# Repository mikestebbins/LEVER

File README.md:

Mike's notes (2016-01-04)
1. schematic and silk screen say 2.2 uF capacitor for C1, but link to part in BOM is for a 2200 pF, or 0.0022 uF
2. 220k resistor spec'd in BOM is WAY too small for pad on board, had to use jumper wire that looks about 50% successful.
3. Arduino code is all for encoder (except for board testing code), but Eagle Board/Schematic files don't seem to have all the necessary hook-ups for encoder to Teensy.
4. May have screwed up and forgot to cut Teensy's trace for battery operation before soldering to board.

# LEVER
####Experiments in electrovibration interaction strategies, inspired by Disney Research papers "Tesla Touch" and "Revel"

Here are the papers I am trying to implement here:
http://www.ivanpoupyrev.com/e-library/2010/teslatouchUIST2010.pdf

http://www.disneyresearch.com/wp-content/uploads/REVEL.pdf

###Summary
Basically, the papers describe a way to augment surfaces with _dynamically changeable tactile properties_ - a surface can change from sticky to slippery basically at will.

###Status
This work is incomplete and ongoing - for one thing, while the circuit decribed here works, I have yet to implement current-sensing feedback as described in the papers. I'm eager to accomplish this because it allows normalization of sensation across people, skin moistures, and time.

###Why I am interested
I'm interested in experimenting with this technology as applied to various notification strategies, particularly on mobile and wearable devices.
I would like to develop interactions in which a person queries a "stack" of stuff waiting for them, rather than being interrupted by a push notification.
The appeal of this technology in this application is that it's totally silent and able to be done without interrupting the person's conversation by stealing focus.
If this technology is implemented on the back of a mobile device, for example, simply rubbing a finger along the back of the phone is all that is needed to see the magnitude of my "stack."
Of course, "stack" can be many things: number of unread emails, number of to-do items, number of places of interest very near me, and so on.

###This repository
The purpose of this repo is to make my work shareable - I had a fair amount of trouble trying to go from the research paper to a safe, working circuit, and I'm hoping to save others some work.

The circuitboard isn't what I would put onto a phone - it is instead a platform for trying out different waveforms, intensities, and so on.

The intent is that you will use the board to figure out the correct implementation details and then generate your own board with a more appropriate layout.

###Requirements
You should follow the BOM pretty precisely unless you know what you are doing. The circuit is designed to work with a 9v battery and I will be trying to allow smaller/more power supplies to work with it. The microcontroller is a Teensy 3.1

###Thanks
I'm so grateful to Disney Research, Ivan Poupyrev, Olivier Bau, and others who worked on the papers for making their work available - I never would have known aobut this cool phoneomenon without their shared work! Thanks as well to nytlabs for supporting my explorations and letting me share in kind.

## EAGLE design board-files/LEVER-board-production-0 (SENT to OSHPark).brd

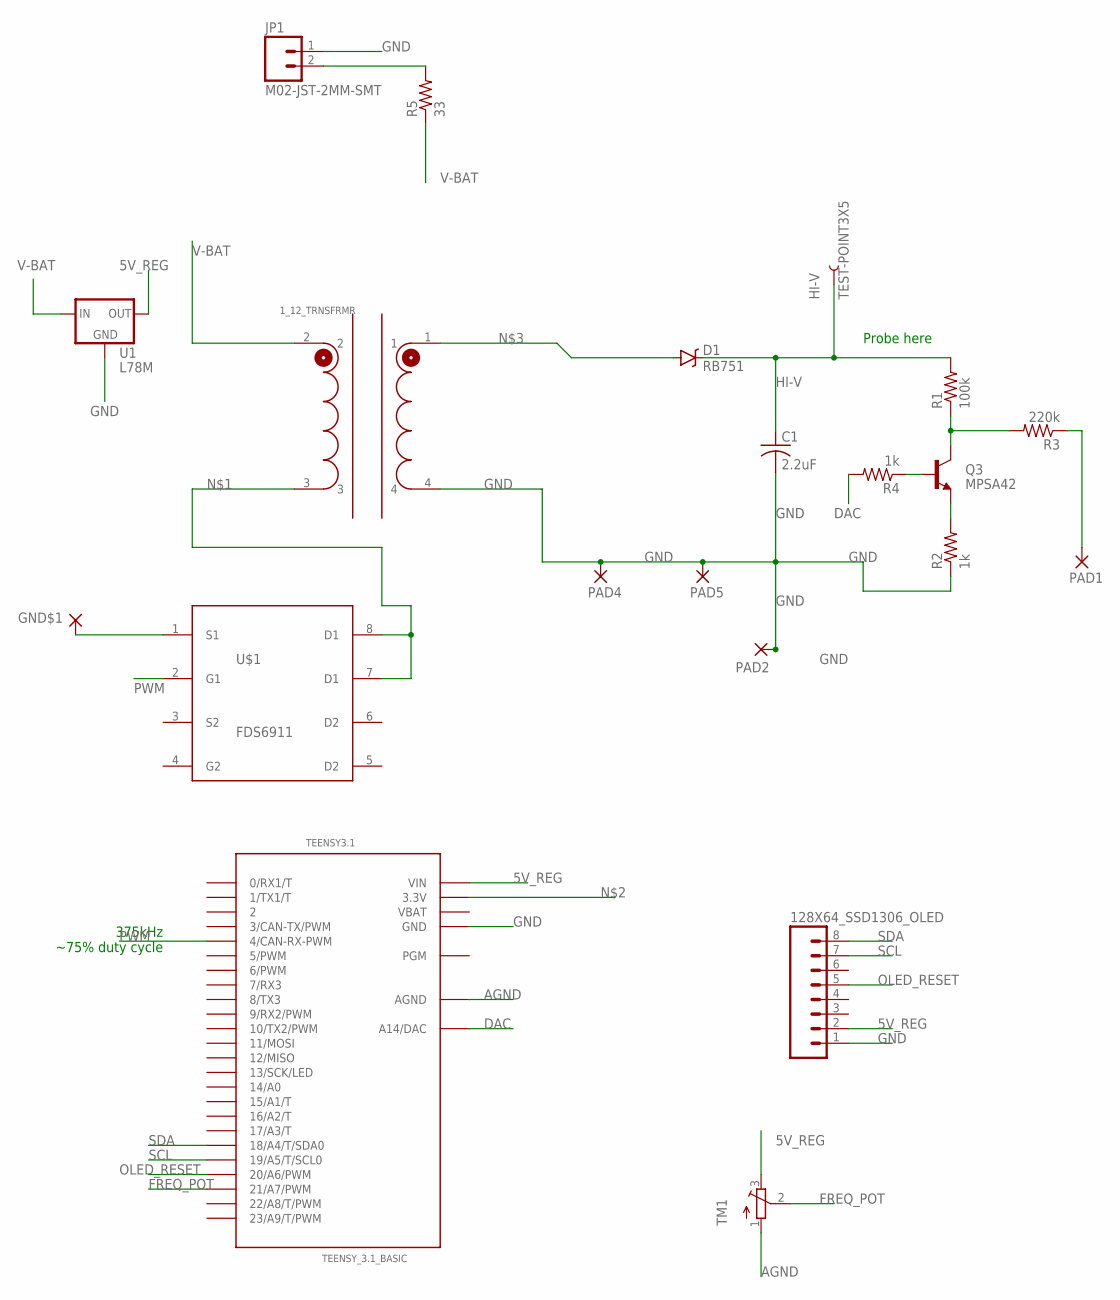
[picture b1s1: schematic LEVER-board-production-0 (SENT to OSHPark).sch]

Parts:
1_12_TRNSFRMR: PA0367
128X64_SSD1306_OLED: M08LOCK; 1X08_LOCK
C1: 2.2uF; C1812
D1: RB751; TO263
GND$1: WIREPADSMD5-2,5; 5-2,5
HI-V: TEST-POINT3X5; PAD.03X.05
JP1: M02-JST-2MM-SMT; JST-2-SMD
PAD1, PAD2, PAD4, PAD5: WIREPADSMD5-2,5; 5-2,5
Q3: MPSA42; TO-92
R1: 100k; R2010
R2, R4: 1k; 1206
R3: 220k; R2010
R5: 33; 1206
TEENSY3.1: TEENSY_3.1_BASIC
TM1: TRIMPOT3386; TRIM-3386
U1: L78M; DPAK
U$1: FDS6911; SO8

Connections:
5V_REG: 128X64_SSD1306_OLED.2, TEENSY3.1.VIN, TM1.3 (E), U1.3 (OUT)
AGND: TEENSY3.1.AGND, TM1.1 (A)
DAC: R4.2, TEENSY3.1.A14 (A14/DAC)
FREQ_POT: TEENSY3.1.21/A7 (21/A7/PWM), TM1.2 (S)
GND: 1_12_TRNSFRMR.4, 128X64_SSD1306_OLED.1, C1.2, GND$1.1, JP1.1 (2), PAD2.1, PAD4.1, PAD5.1, R2.1, TEENSY3.1.GND, TEENSY3.1.GND1 (GND), U1.4 (GND), U$1.1 (S1)
HI-V: C1.1, D1.1 (C), HI-V.P$1, R1.2
unnamed: 1_12_TRNSFRMR.3, U$1.7 (D1), U$1.8 (D1)
unnamed: TEENSY3.1.3.3V, TEENSY3.1.3.3V1 (3.3V)
unnamed: 1_12_TRNSFRMR.1, D1.2 (A)
unnamed: JP1.2 (1), R5.2
unnamed: Q3.1 (C), R1.1, R3.2
unnamed: Q3.3 (E), R2.2
unnamed: Q3.2 (B), R4.1
OLED_RESET: 128X64_SSD1306_OLED.5, TEENSY3.1.20/A6 (20/A6/PWM)
PAD: PAD1.1, R3.1
PWM: TEENSY3.1.4 (4/CAN-RX-PWM), U$1.2 (G1)
SCL: 128X64_SSD1306_OLED.7, TEENSY3.1.19/A5 (19/A5/T/SCL0)
SDA: 128X64_SSD1306_OLED.8, TEENSY3.1.18/A4 (18/A4/T/SDA0)
V-BAT: 1_12_TRNSFRMR.2, R5.1, U1.1 (IN)
VBAT: TEENSY3.1.VBAT

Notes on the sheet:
Probe here
375kHz ~75% duty cycle

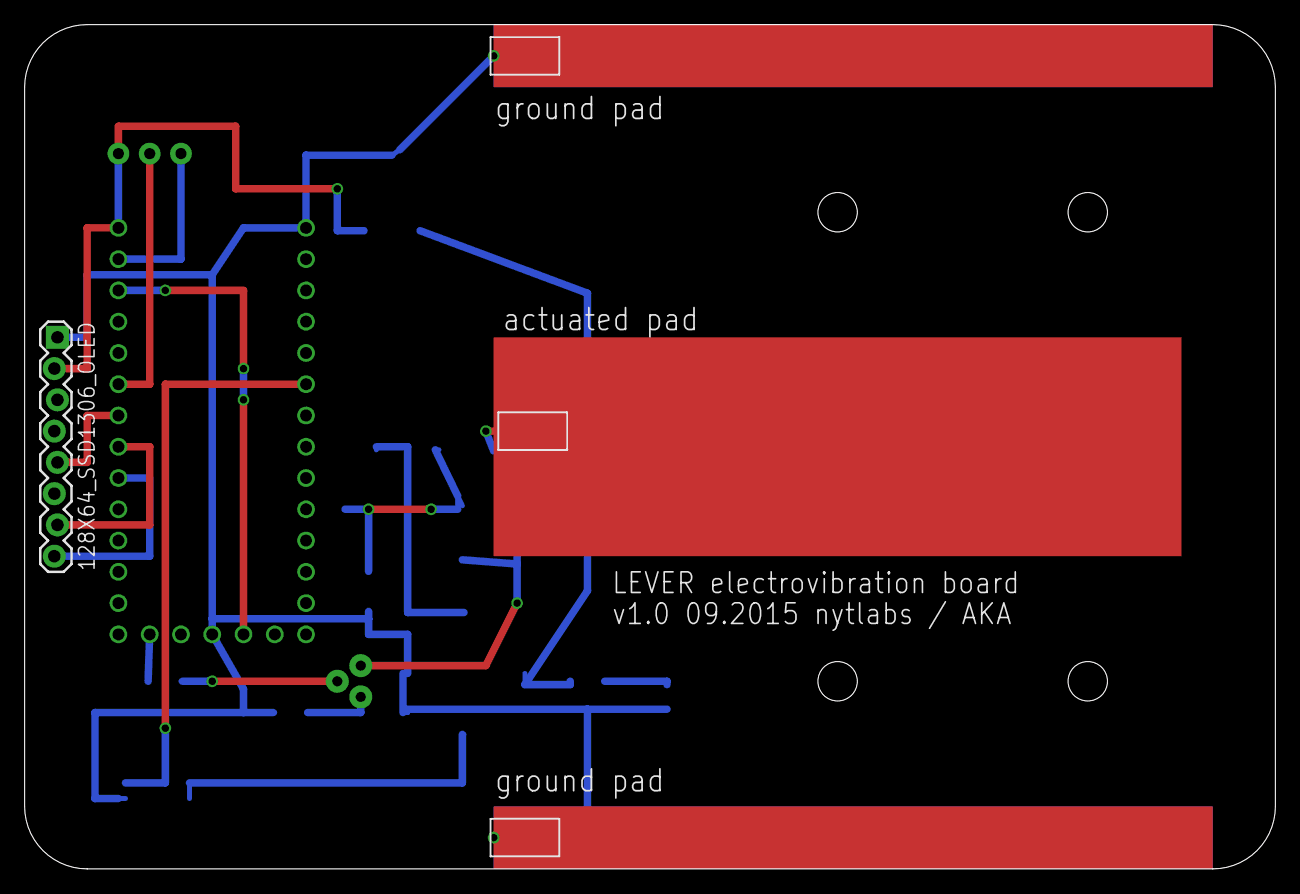
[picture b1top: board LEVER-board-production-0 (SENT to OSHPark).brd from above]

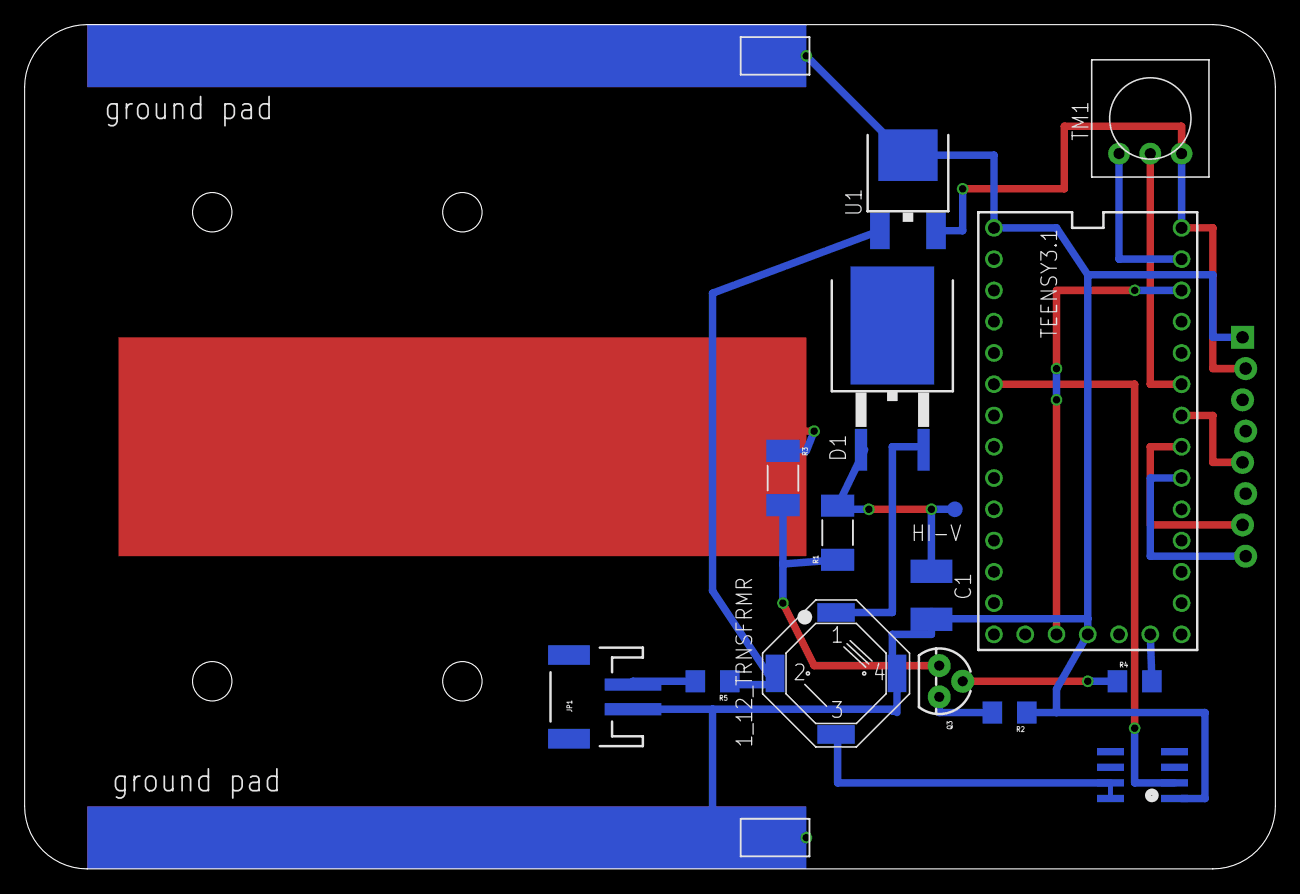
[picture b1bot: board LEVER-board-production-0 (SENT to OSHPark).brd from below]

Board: 2 copper layers, 101.6 x 68.6 mm, 21 parts (17 on the bottom side), 19 nets.

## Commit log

2015-12-18 opened in latest EAGLE sw
2015-12-18 update BOM
2016-01-04 asdfa
2016-01-05 new board top/bottom pdf's on 11x17
2016-01-07 trying to get it to upload
2016-01-13 debugging board not working

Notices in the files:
parts and their libraries:
SparkFun-DiscreteSemi: Licensing: Creative Commons ShareAlike 4.0 International - https://creativecommons.org/licenses/by-sa/4.0
